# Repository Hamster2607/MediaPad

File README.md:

This Macropad has 6 keys for media control and microphone with a rotary encoder for scrolling with qmk firmware. It also has an OLED display.

## Features

  -scrolling up/down
  -muting/unmuting the microphone
  -controlling media(e.g. skip track, pause, previous track)

## BOM
  
| Part                  | Quantity | Price (each) | Total   | Notes                        

 Seeed XIAO RP2040      1       | $6.50        | $6.50   Main MCU                      
 Switches with keycaps  5       | $0.50        | $2.50   TS-style, direct pin          
 Rotary encoder w/button  1     | $1.20        | $1.20   3-pin encoder                 
 OLED display 0.91"     1       | $3.00        | $3.00   4-pin standard display
 3D-printed case        1 set   | $2.00        | $2.00   PLA, ~50 g 
 
Total : ~15.20 USD

## Layout

| SW1 (Undo) | SW2 (Prev) | SW6 (Next) |

| S1 (Mute)  | SW4 (Enter)| SW5 (Play) |

## PCB
This is the schematic for the PCB, made in KiCad

And this is the footprint

## Case

The case will be held tight by 4 M3x16 mm screws and it can be fuly 3D printed

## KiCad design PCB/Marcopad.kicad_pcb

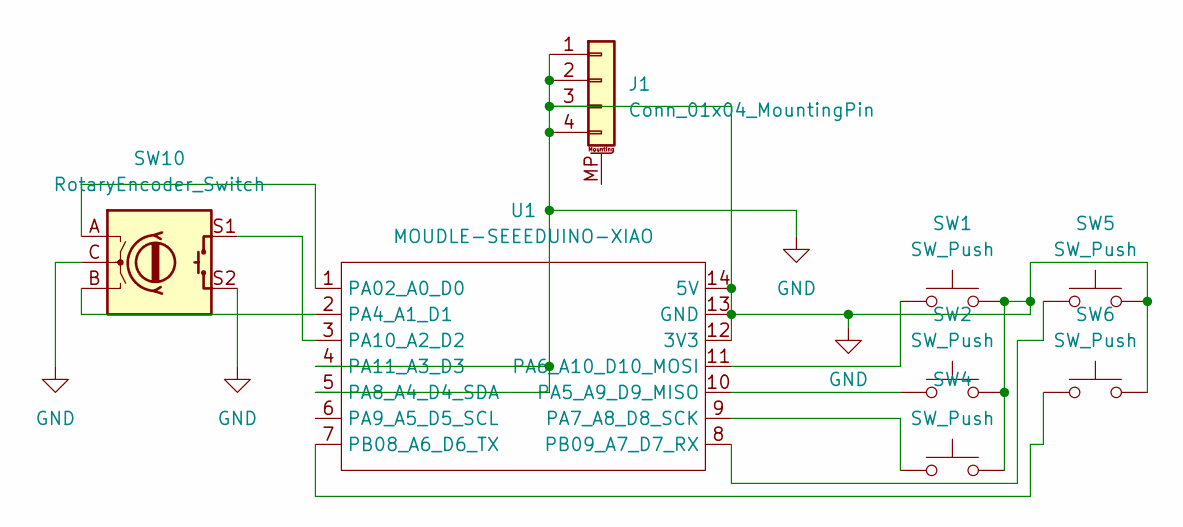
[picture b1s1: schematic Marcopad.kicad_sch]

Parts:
J1: Conn_01x04_MountingPin; PinHeader_1x04_P2.54mm_Vertical
SW1, SW2, SW4, SW5, SW6: SW_Push; SW_Cherry_MX_1.00u_PCB
SW10: RotaryEncoder_Switch; RotaryEncoder_Alps_EC11E-Switch_Vertical_H20mm
U1: MOUDLE-SEEEDUINO-XIAO; XIAO-Generic-Hybrid-14P-2.54-21X17.8MM

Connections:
GND: J1.1, J1.2, J1.3, J1.4, SW1.2, SW2.2, SW4.2, SW5.2, SW6.2, SW10.C, SW10.S2, U1.4 (PA11_A3_D3), U1.5 (PA8_A4_D4_SDA), U1.12 (3V3), U1.13 (GND), U1.14 (5V)
unnamed: SW10.A, U1.1 (PA02_A0_D0)
unnamed: SW10.B, U1.2 (PA4_A1_D1)
unnamed: SW2.1, U1.10 (PA5_A9_D9_MISO)
unnamed: SW1.1, U1.11 (PA6_A10_D10_MOSI)
unnamed: SW4.1, U1.9 (PA7_A8_D8_SCK)
unnamed: SW10.S1, U1.3 (PA10_A2_D2)
unnamed: SW6.1, U1.7 (PB08_A6_D6_TX)
unnamed: SW5.1, U1.8 (PB09_A7_D7_RX)

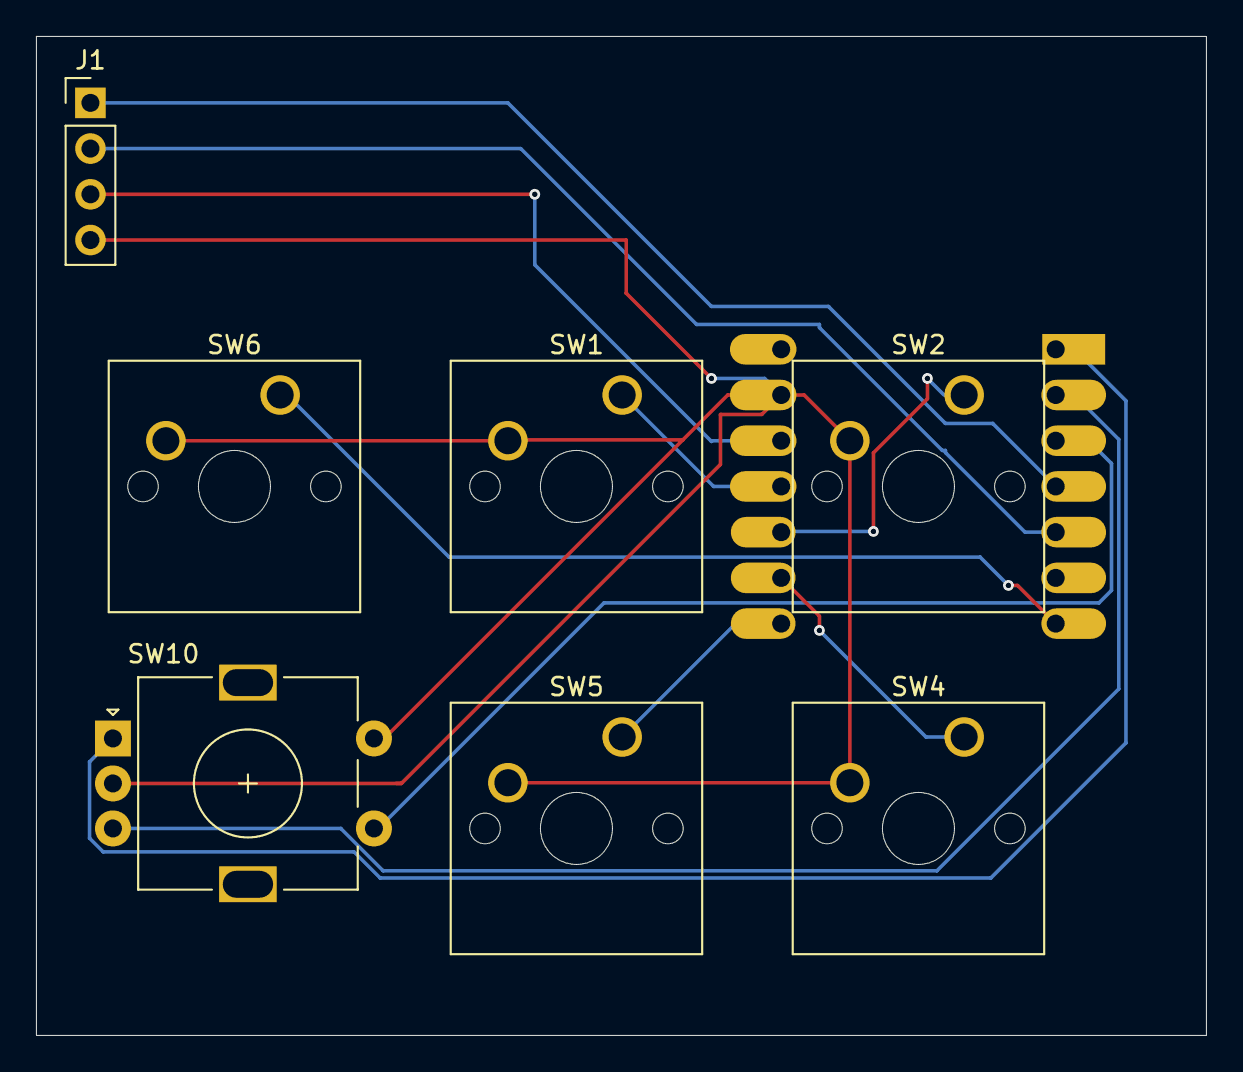
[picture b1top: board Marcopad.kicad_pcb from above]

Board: 2 copper layers, 65.0 x 55.5 mm, 8 parts (1 on the bottom side), 9 nets.

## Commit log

2026-02-19 Initial Hackpad submission
2026-02-19 File system restructure
2026-02-19 Added the case and pcb stl's and also photos!
2026-02-20 Fixed names for the 3rd time...
2026-02-20 Update image paths in README.md to relative links
2026-02-20 Rename screenshots
2026-02-20 New case
